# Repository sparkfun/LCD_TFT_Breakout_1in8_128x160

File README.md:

SparkFun LCD TFT Breakout 1.8" 128x160
========================================

[*LCD TFT Breakout 1.8" 128x160 (LCD-15143)*](https://www.sparkfun.com/products/15143)

A 128x160 color (18 bit!) TFT LCD display breakout with 4-wire SPI interface and microSD card holder. You can use this breakout to easily add visual display/interface capabilities to a project as well as all the storage you might need for multimedia files. 

Repository Contents
-------------------

* **/Documentation** - Data sheets, additional product information
* **/Hardware** - Eagle design files (.brd, .sch)
* **/Production** - Production panel files (.brd)

Documentation
--------------
* **[Library (Top Level)](https://github.com/sparkfun/SparkFun_HyperDisplay)** - Arduino library for general control of 2D visual interfaces.
* **[Library (Mid Level)](https://github.com/sparkfun/HyperDisplay_ILI9163C_ArduinoLibrary)** - Arduino library for all ILI9163 drivers (depends on top level).
* **[Library (Bottom Level)](https://github.com/sparkfun/HyperDisplay_KWH018ST01_4WSPI_ArduinoLibrary)** - Arduino library for the display module used in this breakout (depends on mid level).
* **[Hookup Guide](https://learn.sparkfun.com/tutorials/tft-lcd-breakout-18in-128x160-hookup-guide)** - Basic hookup guide for the LCD TFT Breakout 1.8" 128x160.
* **[SparkFun Fritzing repo](https://github.com/sparkfun/Fritzing_Parts)** - Fritzing diagrams for SparkFun products. 
<!-- * **[SparkFun 3D Model repo](https://github.com/sparkfun/3D_Models)** - 3D models of SparkFun products.  -->
<!-- * **[SparkFun Graphical Datasheets](https://github.com/sparkfun/Graphical_Datasheets)** -Graphical Datasheets for various SparkFun products. -->

Product Versions
----------------
* [LCD-15143](https://www.sparkfun.com/products/15143)

License Information
-------------------

This product is _**open source**_! 

Please review the LICENSE.md file for license information. 

If you have any questions or concerns on licensing, please contact technical support on our [SparkFun forums](https://forum.sparkfun.com/viewforum.php?f=152)

Distributed as-is; no warranty is given.

- Your friends at SparkFun.

_<COLLABORATION CREDIT>_

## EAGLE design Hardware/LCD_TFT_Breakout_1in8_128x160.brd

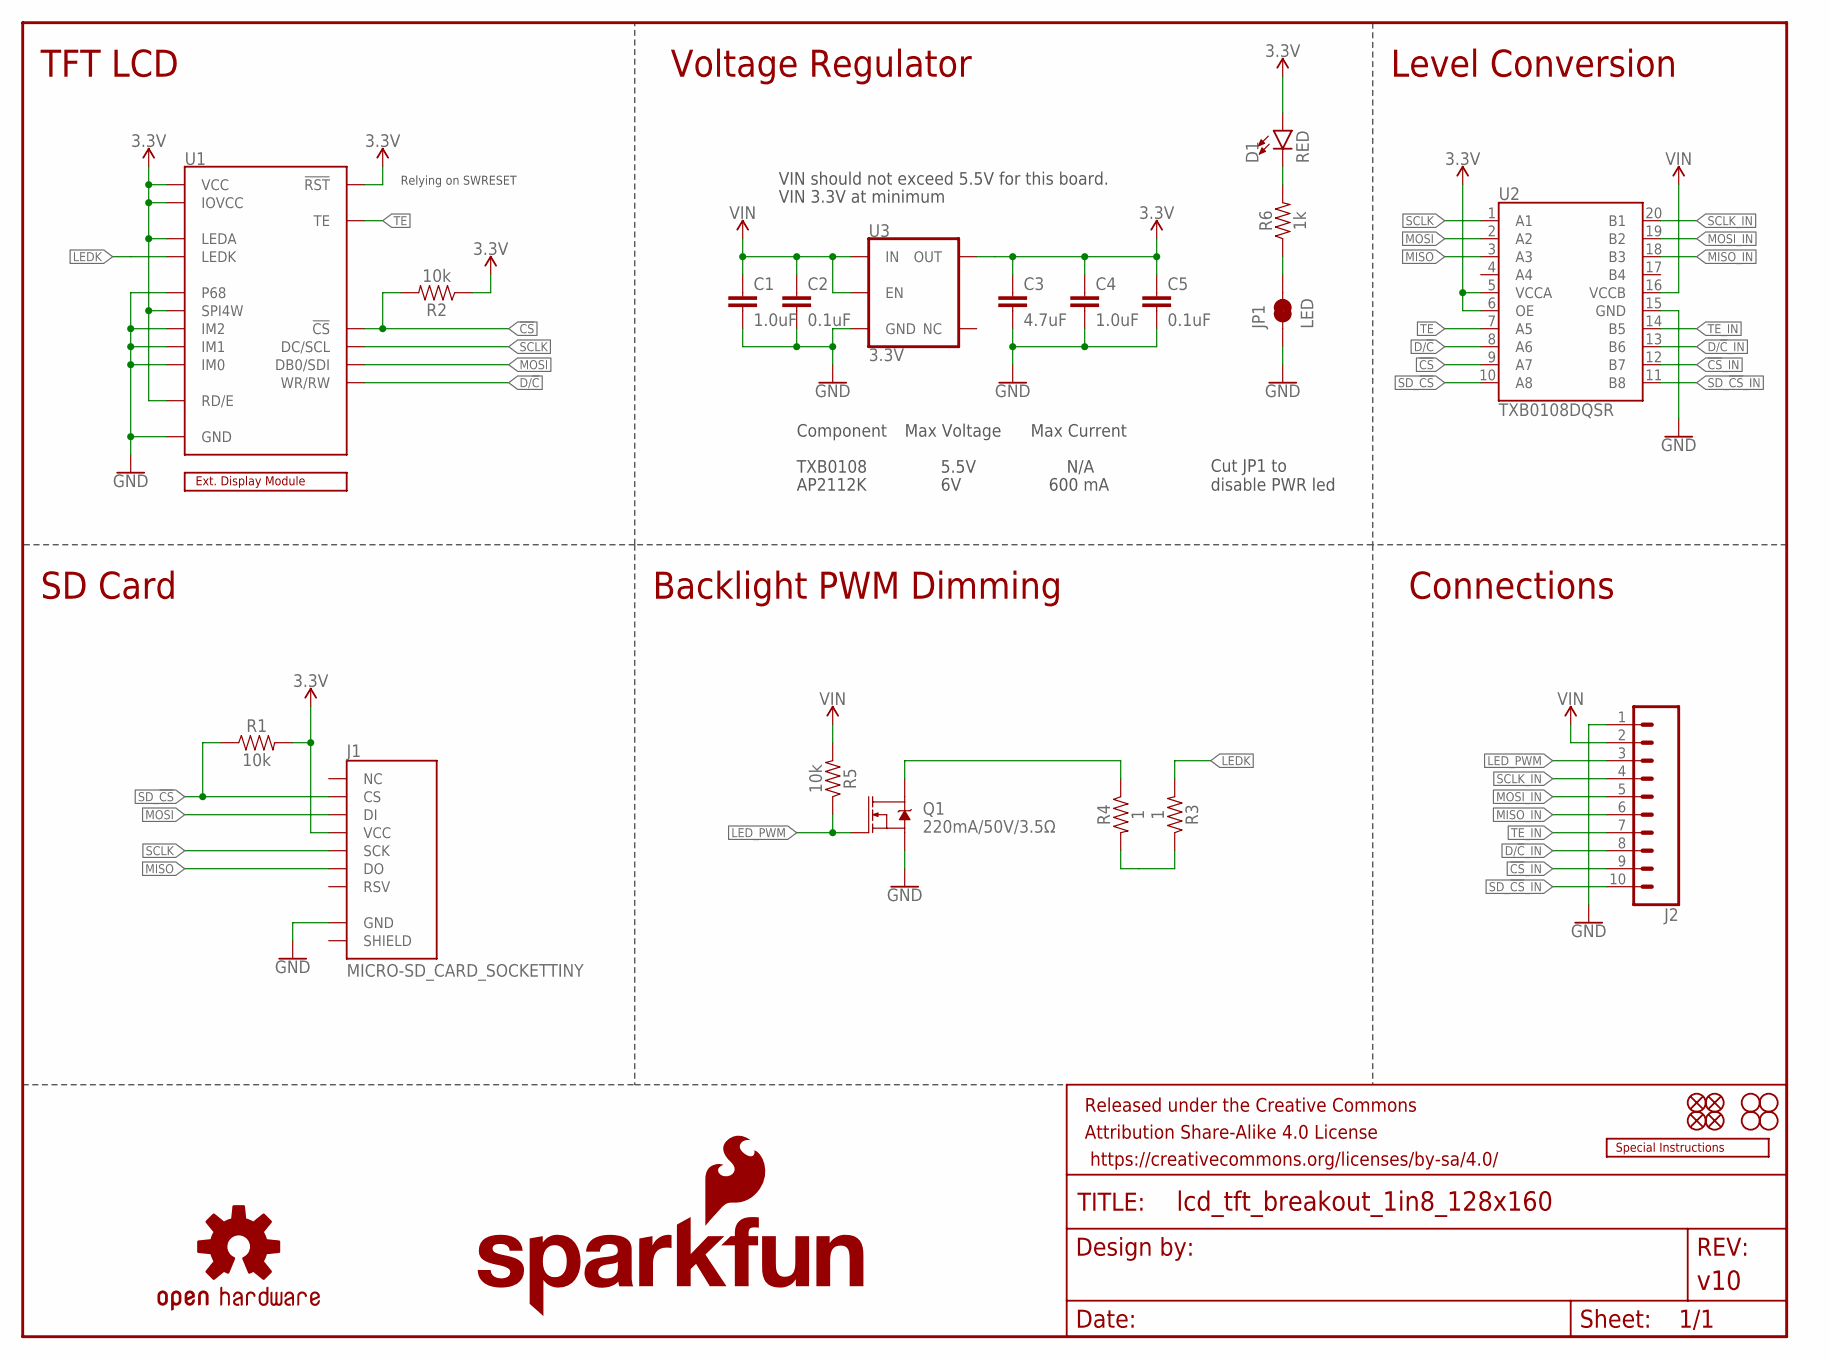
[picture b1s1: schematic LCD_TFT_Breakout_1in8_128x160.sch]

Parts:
C1, C4: 1.0uF; 0603
C2, C5: 0.1uF; 0603
C3: 4.7uF; 0603
D1: RED; LED-0603
FD1, FD2, FD3, FD4: FIDUCIAL1X2; FIDUCIAL-1X2
FRAME1: FRAME-LETTER; CREATIVE_COMMONS
H1, H2, H3, H4: STAND-OFF
J1: MICRO-SD_CARD_SOCKETTINY; MICROSD_TINY
J2: CONN_10NO_SILK_PTH_FEMALE; 1X10_NO_SILK
JP1: LED; SMT-JUMPER_2_NC_TRACE_SILK
LOGO1: SFE_LOGO_NAME_FLAME.3_INCH; SFE_LOGO_NAME_FLAME_.3
LOGO2: SPECIAL_INSTRUCTIONS-PRODUCTION; PRODUCTION_INSTRUCTIONS
LOGO3: OSHW-LOGOS; OSHW-LOGO-S
Q1: 220mA/50V/3.5Ω; SOT23-3
R1, R2, R5: 10k; 0603
R3, R4: 1; 0603
R6: 1k; 0603
U1: KWH018ST14-F01_4WSPI-BOTTOM; FPC05040-17204
U2: TXB0108DQSR; UFDFN-20
U3: 3.3V; SOT23-5
U$33: EXTERNAL_DISP-KWH018ST14-F01; KWH018ST14-F01_HOLES

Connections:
3.3V: C3.1, C4.1, C5.1, D1.A, J1.4 (VCC), R1.2, R2.1, U1.P$1 (LEDA), U1.P$4 (!RST), U1.P$5 (VCC), U1.P$6 (IOVCC), U1.P$26 (RD/E), U1.P$30 (SPI4W), U2.5 (VCCA), U2.6 (OE), U3.5 (OUT)
!CS: R2.2, U1.P$29 (!CS), U2.9 (A7)
!CS!_IN: J2.9, U2.12 (B7)
D/!C: U1.P$27 (WR/RW), U2.8 (A6)
D/!C!_IN: J2.8, U2.13 (B6)
GND: C1.2, C2.2, C3.2, C4.2, C5.2, J1.6 (GND), J2.1, JP1.1, Q1.2 (S), U1.P$3 (GND), U1.P$8 (GND), U1.P$9 (GND), U1.P$10 (GND), U1.P$11 (GND), U1.P$12 (GND), U1.P$13 (GND), U1.P$14 (GND), U1.P$15 (GND), U1.P$16 (GND), U1.P$17 (GND), U1.P$18 (GND), U1.P$19 (GND), U1.P$20 (GND), U1.P$21 (GND), U1.P$22 (GND), U1.P$23 (GND), U1.P$24 (GND), U1.P$31 (P68), U1.P$32 (IM2), U1.P$33 (IM1), U1.P$34 (IM0), U1.P$35 (GND), U1.P$40 (GND), U2.15 (GND), U3.2 (GND)
LEDK: R3.2, U1.P$2 (LEDK)
LED_PWM: J2.3, Q1.1 (G), R5.1
MISO: J1.7 (DO), U2.3 (A3)
MISO_IN: J2.6, U2.18 (B3)
MOSI: J1.3 (DI), U1.P$25 (DB0/SDI), U2.2 (A2)
MOSI_IN: J2.5, U2.19 (B2)
unnamed: D1.C, R6.2
unnamed: JP1.2, R6.1
unnamed: R3.1, R4.2
unnamed: Q1.3 (D), R4.1
SCLK: J1.5 (SCK), U1.P$28 (DC/SCL), U2.1 (A1)
SCLK_IN: J2.4, U2.20 (B1)
SD_!CS: J1.2 (CS), R1.1, U2.10 (A8)
SD_!CS!_IN: J2.10, U2.11 (B8)
TE: U1.P$7 (TE), U2.7 (A5)
TE_IN: J2.7, U2.14 (B5)
VIN: C1.1, C2.1, J2.2, R5.2, U2.16 (VCCB), U3.1 (IN), U3.3 (EN)

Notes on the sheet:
Voltage Regulator
Level Conversion
Backlight PWM Dimming
Relying on SWRESET
TFT LCD
Connections
SD Card
VIN should not exceed 5.5V for this board.
Component
Max Voltage
TXB0108
AP2112K
Max Current
600 mA
N/A
5.5V
Cut JP1 to disable PWR led
VIN 3.3V at minimum

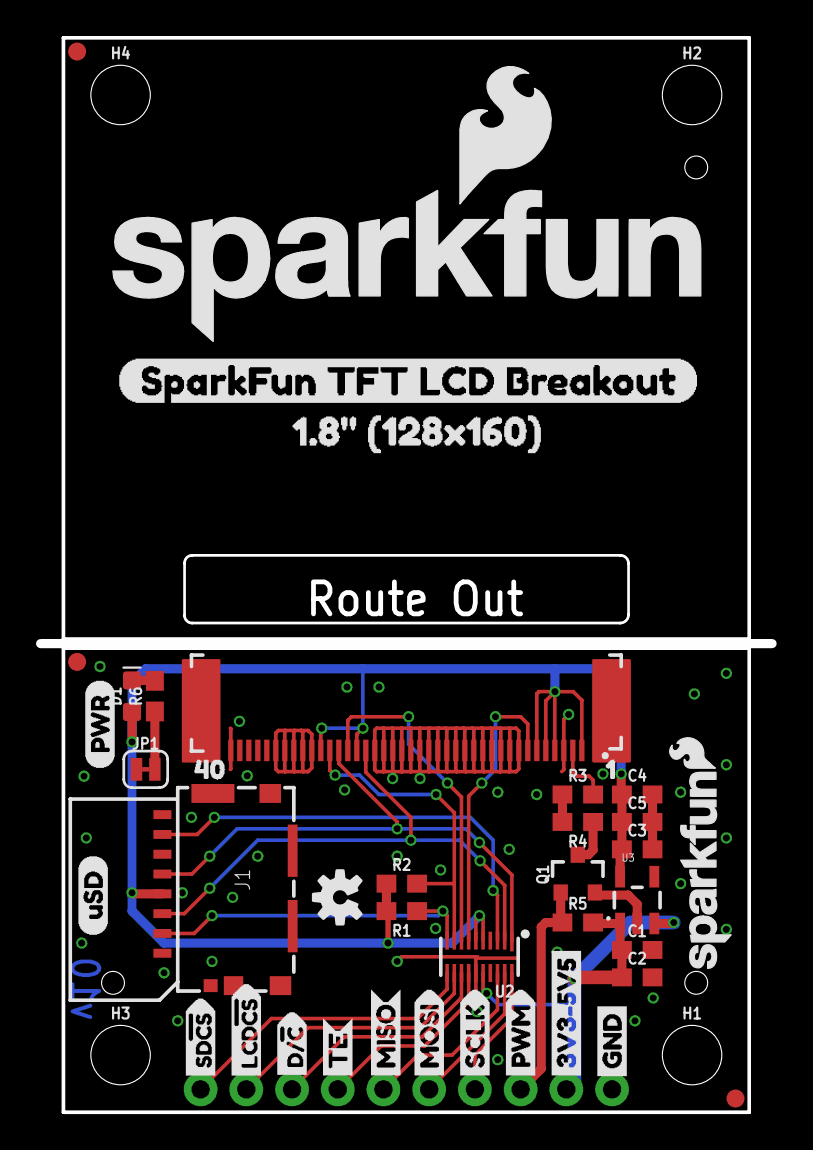
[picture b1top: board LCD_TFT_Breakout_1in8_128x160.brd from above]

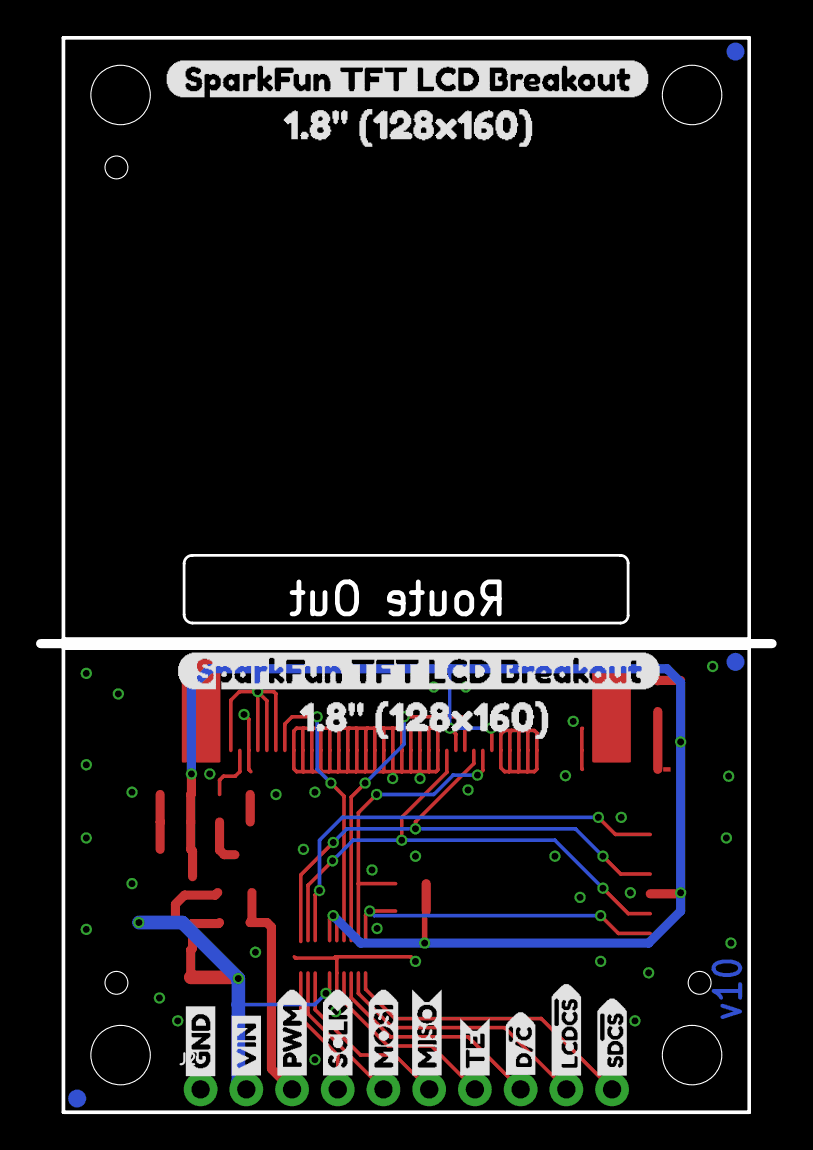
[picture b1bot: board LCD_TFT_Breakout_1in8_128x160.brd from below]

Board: 2 copper layers, 40.6 x 59.4 mm, 66 parts (19 on the bottom side), 23 nets.

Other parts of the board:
FD5, FD6: FIDUCIAL1X2; FIDUCIAL-1X2
U$1: 3V3#5V50
U$2: SFE_LOGO_NAME_.1
U$3: SFE_LOGO_FLAME_.1
U$4: USD2
U$5, U$6: LCD#CS1
U$7, U$25: D##C7
U$8, U$16: SD#CS0
U$9, U$32: GND0
U$10: VIN1
U$11, U$26: MISO3
U$12, U$27: MOSI2
U$13, U$28: SCLK4
U$14, U$29: TE5
U$15, U$30: PWM6
U$17: 10
U$18: PWR4
U$19: SPARKFUN_TFT_LCD_BREAKOUT1
U$20: 1#8#_#128X160#1
U$21, U$23: SPARKFUN_TFT_LCD_BREAKOUT2
U$22, U$24: 1#8#_#128X160#0
U$31: 401

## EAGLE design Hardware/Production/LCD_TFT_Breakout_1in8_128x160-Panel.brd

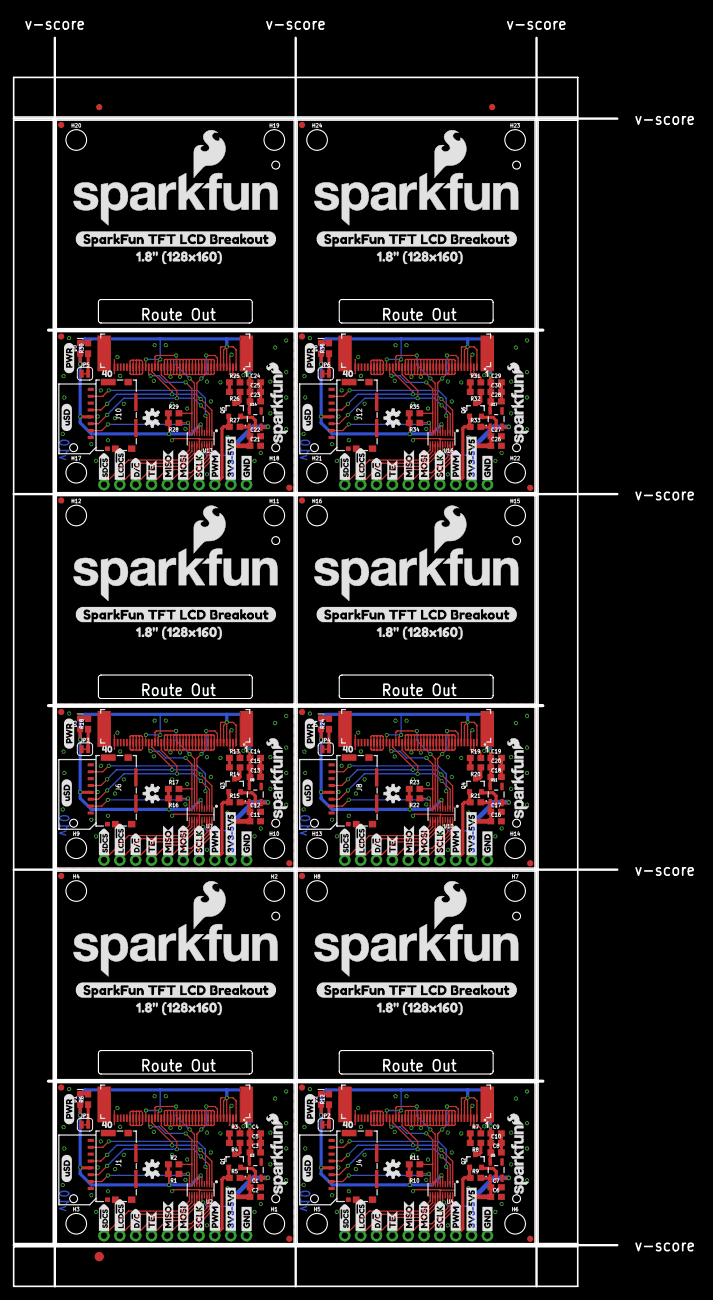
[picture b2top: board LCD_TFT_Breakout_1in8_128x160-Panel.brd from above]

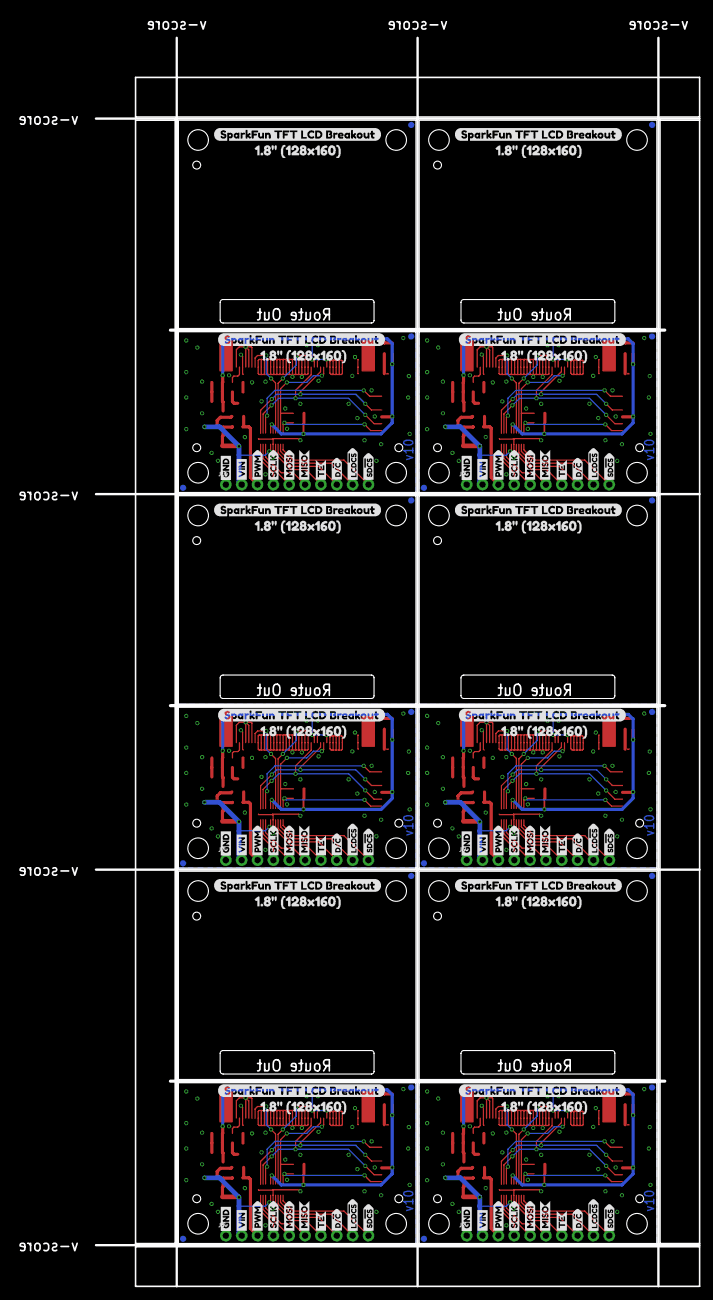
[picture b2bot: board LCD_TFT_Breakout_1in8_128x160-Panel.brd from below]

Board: 2 copper layers, 109.8 x 203.9 mm, 399 parts (114 on the bottom side), 138 nets.

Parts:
C1, C4, C7, C9, C12, C14, C17, C19, C22, C24, C27, C29: 1.0uF; 0603
C2, C5, C6, C10, C11, C15, C16, C20, C21, C25, C26, C30: 0.1uF; 0603
C3, C8, C13, C18, C23, C28: 4.7uF; 0603
D1, D2, D3, D4, D5, D6: RED; LED-0603
E$1, E$2: FIDUCIAL-1X2
E$3: FIDUCIAL-1.5X3
FD1, FD2, FD3, FD4, FD5, FD6, FD7, FD8, FD9, FD10, FD11, FD12, FD13, FD14, FD15, FD16, FD17, FD18, FD19, FD20, FD21, FD22, FD23, FD24, FD25, FD26, FD27, FD28, FD29, FD30, FD31, FD32, FD33, FD34, FD35, FD36: FIDUCIAL1X2; FIDUCIAL-1X2
FRAME1, FRAME2, FRAME3, FRAME4, FRAME5, FRAME6: FRAME-LETTER; CREATIVE_COMMONS
H1, H2, H3, H4, H5, H6, H7, H8, H9, H10, H11, H12, H13, H14, H15, H16, H17, H18, H19, H20, H21, H22, H23, H24: STAND-OFF
J1, J4, J6, J8, J10, J12: MICRO-SD_CARD_SOCKETTINY; MICROSD_TINY
J2, J3, J5, J7, J9, J11: 1X10_NO_SILK
JP1, JP2, JP3, JP4, JP5, JP6: LED; SMT-JUMPER_2_NC_TRACE_SILK
LOGO1, LOGO5, LOGO8, LOGO11, LOGO14, LOGO17: SFE_LOGO_NAME_FLAME.3_INCH; SFE_LOGO_NAME_FLAME_.3
LOGO2, LOGO4, LOGO7, LOGO10, LOGO13, LOGO16: SPECIAL_INSTRUCTIONS-PRODUCTION; PRODUCTION_INSTRUCTIONS
LOGO3, LOGO6, LOGO9, LOGO12, LOGO15, LOGO18: OSHW-LOGOS; OSHW-LOGO-S
Q1, Q2, Q3, Q4, Q5, Q6: 220mA/50V/3.5Ω; SOT23-3
R1, R2, R5, R9, R10, R11, R15, R16, R17, R21, R22, R23, R27, R28, R29, R33, R34, R35: 10k; 0603
R3, R4, R7, R8, R13, R14, R19, R20, R25, R26, R31, R32: 1; 0603
R6, R12, R18, R24, R30, R36: 1k; 0603
U1, U6, U9, U12, U15, U18: FPC05040-17204
U2, U4, U7, U10, U13, U16: TXB0108DQSR; UFDFN-20
U3, U5, U8, U11, U14, U17: 3.3V; SOT23-5
U$1, U$64, U$97, U$130, U$163, U$196: 3V3#5V50
U$2, U$34, U$67, U$100, U$133, U$166: SFE_LOGO_NAME_.1
U$3, U$35, U$68, U$101, U$134, U$167: SFE_LOGO_FLAME_.1
U$4, U$61, U$94, U$127, U$160, U$193: USD2
U$5, U$6, U$57, U$58, U$90, U$91, U$123, U$124, U$156, U$157, U$189, U$190: LCD#CS1
U$7, U$25, U$36, U$50, U$69, U$83, U$102, U$116, U$135, U$149, U$168, U$182: D##C7
U$8, U$16, U$59, U$60, U$92, U$93, U$125, U$126, U$158, U$159, U$191, U$192: SD#CS0
U$9, U$32, U$37, U$56, U$70, U$89, U$103, U$122, U$136, U$155, U$169, U$188: GND0
U$10, U$38, U$71, U$104, U$137, U$170: VIN1
U$11, U$26, U$39, U$51, U$72, U$84, U$105, U$117, U$138, U$150, U$171, U$183: MISO3
U$12, U$27, U$40, U$52, U$73, U$85, U$106, U$118, U$139, U$151, U$172, U$184: MOSI2
U$13, U$28, U$41, U$53, U$74, U$86, U$107, U$119, U$140, U$152, U$173, U$185: SCLK4
U$14, U$29, U$42, U$54, U$75, U$87, U$108, U$120, U$141, U$153, U$174, U$186: TE5
U$15, U$30, U$43, U$55, U$76, U$88, U$109, U$121, U$142, U$154, U$175, U$187: PWM6
U$17, U$65, U$98, U$131, U$164, U$197: 10
U$18, U$62, U$95, U$128, U$161, U$194: PWR4
U$19, U$44, U$77, U$110, U$143, U$176: SPARKFUN_TFT_LCD_BREAKOUT1
U$20, U$45, U$78, U$111, U$144, U$177: 1#8#_#128X160#1
U$21, U$23, U$46, U$48, U$79, U$81, U$112, U$114, U$145, U$147, U$178, U$180: SPARKFUN_TFT_LCD_BREAKOUT2
U$22, U$24, U$47, U$49, U$80, U$82, U$113, U$115, U$146, U$148, U$179, U$181: 1#8#_#128X160#0
U$31, U$66, U$99, U$132, U$165, U$198: 401
U$33, U$63, U$96, U$129, U$162, U$195: EXTERNAL_DISP-KWH018ST14-F01; KWH018ST14-F01_HOLES

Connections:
3.3V: C3.1, C4.1, C5.1, D1.A, J1.4, R1.2, R2.1, U1.P$1, U1.P$4, U1.P$5, U1.P$6, U1.P$26, U1.P$30, U2.5, U2.6, U3.5
3.3V1: C8.1, C9.1, C10.1, D2.A, J4.4, R10.2, R11.1, U4.5, U4.6, U5.5, U6.P$1, U6.P$4, U6.P$5, U6.P$6, U6.P$26, U6.P$30
3.3V2: C13.1, C14.1, C15.1, D3.A, J6.4, R16.2, R17.1, U7.5, U7.6, U8.5, U9.P$1, U9.P$4, U9.P$5, U9.P$6, U9.P$26, U9.P$30
3.3V3: C18.1, C19.1, C20.1, D4.A, J8.4, R22.2, R23.1, U10.5, U10.6, U11.5, U12.P$1, U12.P$4, U12.P$5, U12.P$6, U12.P$26, U12.P$30
3.3V4: C23.1, C24.1, C25.1, D5.A, J10.4, R28.2, R29.1, U13.5, U13.6, U14.5, U15.P$1, U15.P$4, U15.P$5, U15.P$6, U15.P$26, U15.P$30
3.3V5: C28.1, C29.1, C30.1, D6.A, J12.4, R34.2, R35.1, U16.5, U16.6, U17.5, U18.P$1, U18.P$4, U18.P$5, U18.P$6, U18.P$26, U18.P$30
!CS: R2.2, U1.P$29, U2.9
!CS1: R11.2, U4.9, U6.P$29
!CS2: R17.2, U7.9, U9.P$29
!CS3: R23.2, U10.9, U12.P$29
!CS4: R29.2, U13.9, U15.P$29
!CS5: R35.2, U16.9, U18.P$29
!CS!_IN: J2.9, U2.12
!CS!_IN1: J3.9, U4.12
!CS!_IN2: J5.9, U7.12
!CS!_IN3: J7.9, U10.12
!CS!_IN4: J9.9, U13.12
!CS!_IN5: J11.9, U16.12
D/!C: U1.P$27, U2.8
D/!C1: U4.8, U6.P$27
D/!C2: U7.8, U9.P$27
D/!C3: U10.8, U12.P$27
D/!C4: U13.8, U15.P$27
D/!C5: U16.8, U18.P$27
D/!C!_IN: J2.8, U2.13
D/!C!_IN1: J3.8, U4.13
D/!C!_IN2: J5.8, U7.13
D/!C!_IN3: J7.8, U10.13
D/!C!_IN4: J9.8, U13.13
D/!C!_IN5: J11.8, U16.13
GND: C1.2, C2.2, C3.2, C4.2, C5.2, J1.6, J2.1, JP1.1, Q1.2, U1.P$3, U1.P$8, U1.P$9, U1.P$10, U1.P$11, U1.P$12, U1.P$13, U1.P$14, U1.P$15, U1.P$16, U1.P$17, U1.P$18, U1.P$19, U1.P$20, U1.P$21, U1.P$22, U1.P$23, U1.P$24, U1.P$31, U1.P$32, U1.P$33, U1.P$34, U1.P$35, U1.P$40, U2.15, U3.2
GND1: C6.2, C7.2, C8.2, C9.2, C10.2, J3.1, J4.6, JP2.1, Q2.2, U4.15, U5.2, U6.P$3, U6.P$8, U6.P$9, U6.P$10, U6.P$11, U6.P$12, U6.P$13, U6.P$14, U6.P$15, U6.P$16, U6.P$17, U6.P$18, U6.P$19, U6.P$20, U6.P$21, U6.P$22, U6.P$23, U6.P$24, U6.P$31, U6.P$32, U6.P$33, U6.P$34, U6.P$35, U6.P$40
GND2: C11.2, C12.2, C13.2, C14.2, C15.2, J5.1, J6.6, JP3.1, Q3.2, U7.15, U8.2, U9.P$3, U9.P$8, U9.P$9, U9.P$10, U9.P$11, U9.P$12, U9.P$13, U9.P$14, U9.P$15, U9.P$16, U9.P$17, U9.P$18, U9.P$19, U9.P$20, U9.P$21, U9.P$22, U9.P$23, U9.P$24, U9.P$31, U9.P$32, U9.P$33, U9.P$34, U9.P$35, U9.P$40
GND3: C16.2, C17.2, C18.2, C19.2, C20.2, J7.1, J8.6, JP4.1, Q4.2, U10.15, U11.2, U12.P$3, U12.P$8, U12.P$9, U12.P$10, U12.P$11, U12.P$12, U12.P$13, U12.P$14, U12.P$15, U12.P$16, U12.P$17, U12.P$18, U12.P$19, U12.P$20, U12.P$21, U12.P$22, U12.P$23, U12.P$24, U12.P$31, U12.P$32, U12.P$33, U12.P$34, U12.P$35, U12.P$40
GND4: C21.2, C22.2, C23.2, C24.2, C25.2, J9.1, J10.6, JP5.1, Q5.2, U13.15, U14.2, U15.P$3, U15.P$8, U15.P$9, U15.P$10, U15.P$11, U15.P$12, U15.P$13, U15.P$14, U15.P$15, U15.P$16, U15.P$17, U15.P$18, U15.P$19, U15.P$20, U15.P$21, U15.P$22, U15.P$23, U15.P$24, U15.P$31, U15.P$32, U15.P$33, U15.P$34, U15.P$35, U15.P$40
GND5: C26.2, C27.2, C28.2, C29.2, C30.2, J11.1, J12.6, JP6.1, Q6.2, U16.15, U17.2, U18.P$3, U18.P$8, U18.P$9, U18.P$10, U18.P$11, U18.P$12, U18.P$13, U18.P$14, U18.P$15, U18.P$16, U18.P$17, U18.P$18, U18.P$19, U18.P$20, U18.P$21, U18.P$22, U18.P$23, U18.P$24, U18.P$31, U18.P$32, U18.P$33, U18.P$34, U18.P$35, U18.P$40
LEDK: R3.2, U1.P$2
LEDK1: R7.2, U6.P$2
LEDK2: R13.2, U9.P$2
LEDK3: R19.2, U12.P$2
LEDK4: R25.2, U15.P$2
LEDK5: R31.2, U18.P$2
LED_PWM: J2.3, Q1.1, R5.1
LED_PWM1: J3.3, Q2.1, R9.1
LED_PWM2: J5.3, Q3.1, R15.1
LED_PWM3: J7.3, Q4.1, R21.1
LED_PWM4: J9.3, Q5.1, R27.1
LED_PWM5: J11.3, Q6.1, R33.1
MISO: J1.7, U2.3
MISO1: J4.7, U4.3
MISO2: J6.7, U7.3
MISO3: J8.7, U10.3
MISO4: J10.7, U13.3
MISO5: J12.7, U16.3
MISO_IN: J2.6, U2.18
MISO_IN1: J3.6, U4.18
MISO_IN2: J5.6, U7.18
MISO_IN3: J7.6, U10.18
MISO_IN4: J9.6, U13.18
MISO_IN5: J11.6, U16.18
MOSI: J1.3, U1.P$25, U2.2
MOSI1: J4.3, U4.2, U6.P$25
MOSI2: J6.3, U7.2, U9.P$25
MOSI3: J8.3, U10.2, U12.P$25
MOSI4: J10.3, U13.2, U15.P$25
MOSI5: J12.3, U16.2, U18.P$25
MOSI_IN: J2.5, U2.19
MOSI_IN1: J3.5, U4.19
MOSI_IN2: J5.5, U7.19
MOSI_IN3: J7.5, U10.19
MOSI_IN4: J9.5, U13.19
MOSI_IN5: J11.5, U16.19
unnamed: D1.C, R6.2
unnamed: JP1.2, R6.1
unnamed: R3.1, R4.2
unnamed: Q2.3, R8.1
unnamed: Q1.3, R4.1
unnamed: D2.C, R12.2
unnamed: JP2.2, R12.1
unnamed: R7.1, R8.2
unnamed: Q3.3, R14.1
unnamed: D3.C, R18.2
unnamed: JP3.2, R18.1
unnamed: R13.1, R14.2
unnamed: Q4.3, R20.1
unnamed: D4.C, R24.2
unnamed: JP4.2, R24.1
unnamed: R19.1, R20.2
unnamed: Q5.3, R26.1
unnamed: D5.C, R30.2
unnamed: JP5.2, R30.1
unnamed: R25.1, R26.2
unnamed: Q6.3, R32.1
unnamed: D6.C, R36.2
unnamed: JP6.2, R36.1
unnamed: R31.1, R32.2
SCLK: J1.5, U1.P$28, U2.1
SCLK1: J4.5, U4.1, U6.P$28
SCLK2: J6.5, U7.1, U9.P$28
SCLK3: J8.5, U10.1, U12.P$28
SCLK4: J10.5, U13.1, U15.P$28
SCLK5: J12.5, U16.1, U18.P$28
SCLK_IN: J2.4, U2.20
SCLK_IN1: J3.4, U4.20
SCLK_IN2: J5.4, U7.20
SCLK_IN3: J7.4, U10.20
SCLK_IN4: J9.4, U13.20
SCLK_IN5: J11.4, U16.20
SD_!CS: J1.2, R1.1, U2.10
SD_!CS1: J4.2, R10.1, U4.10
SD_!CS2: J6.2, R16.1, U7.10
SD_!CS3: J8.2, R22.1, U10.10
SD_!CS4: J10.2, R28.1, U13.10
SD_!CS5: J12.2, R34.1, U16.10
SD_!CS!_IN: J2.10, U2.11
SD_!CS!_IN1: J3.10, U4.11
SD_!CS!_IN2: J5.10, U7.11
SD_!CS!_IN3: J7.10, U10.11
SD_!CS!_IN4: J9.10, U13.11
SD_!CS!_IN5: J11.10, U16.11
TE: U1.P$7, U2.7
TE1: U4.7, U6.P$7
TE2: U7.7, U9.P$7
TE3: U10.7, U12.P$7
TE4: U13.7, U15.P$7
TE5: U16.7, U18.P$7
TE_IN: J2.7, U2.14
TE_IN1: J3.7, U4.14
TE_IN2: J5.7, U7.14
TE_IN3: J7.7, U10.14
TE_IN4: J9.7, U13.14
TE_IN5: J11.7, U16.14
VIN: C1.1, C2.1, J2.2, R5.2, U2.16, U3.1, U3.3
VIN1: C6.1, C7.1, J3.2, R9.2, U4.16, U5.1, U5.3
VIN2: C11.1, C12.1, J5.2, R15.2, U7.16, U8.1, U8.3
VIN3: C16.1, C17.1, J7.2, R21.2, U10.16, U11.1, U11.3
VIN4: C21.1, C22.1, J9.2, R27.2, U13.16, U14.1, U14.3
VIN5: C26.1, C27.1, J11.2, R33.2, U16.16, U17.1, U17.3

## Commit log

2018-12-18 Change to SD from SPI flash
2018-12-19 Move old checklist reports to folder
2018-12-19 Add new Buzzard labels
2018-12-19 Small fixes/tweaks according to checklist
2018-12-19 Create new checklist report
2018-12-19 Improve ground plane continuity
2018-12-20 Perform Proto Review task items
    Completes and closes issue #1
2018-12-21 Perform checklist after proto review
2018-12-21 Panelize and CAM prototypes
2019-01-02 Fix silkscreen and bump out SD card 50 mil
2019-01-02 Reduce strain on FPC cable
    Acheived by moving the connector toward the PTH row by 40 mil. Route out area moved flush with v-score and also narrowed a little bit
2019-01-02 Minor touch-ups (trace routing, silk placement etc)
2019-01-03 Fixed Reds Design Review Issues
    As shown in isse #2
    - Offset route-out from v-score
    - Added FPC numbers in silk
    - Additional little silk rearrangements/tweaking
2019-01-03 Make output connector look prettier in schematic
2019-01-03 Update version to v10
2019-01-03 Remove wire stubs
2019-01-03 Finished checklist after design review
2019-01-03 Address issue #3
    Removed unnecessary via on cs line
    Linked via under SD socket to GND net
    Cleared one wire stub DRC error and approved remaining
2019-01-07 Fill out README
2019-01-08 Move route out to dimension layer per gerber review
2019-01-08 Set DRC to fab limit
2019-01-09 panel

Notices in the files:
parts and their libraries:
SparkFun-Aesthetics: Licensing: Creative Commons ShareAlike 4.0 International - https://creativecommons.org/licenses/by-sa/4.0
SparkFun-Aesthetics: Released under the Creative Commons Attribution Share-Alike 4.0 License
SparkFun-Aesthetics: https://creativecommons.org/licenses/by-sa/4.0
